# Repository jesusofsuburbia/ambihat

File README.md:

# Ambihat

### Raspberry Pi Hat to connect neopixels as ambilight and an IR receiver to remote control Kodi

... description follows ...

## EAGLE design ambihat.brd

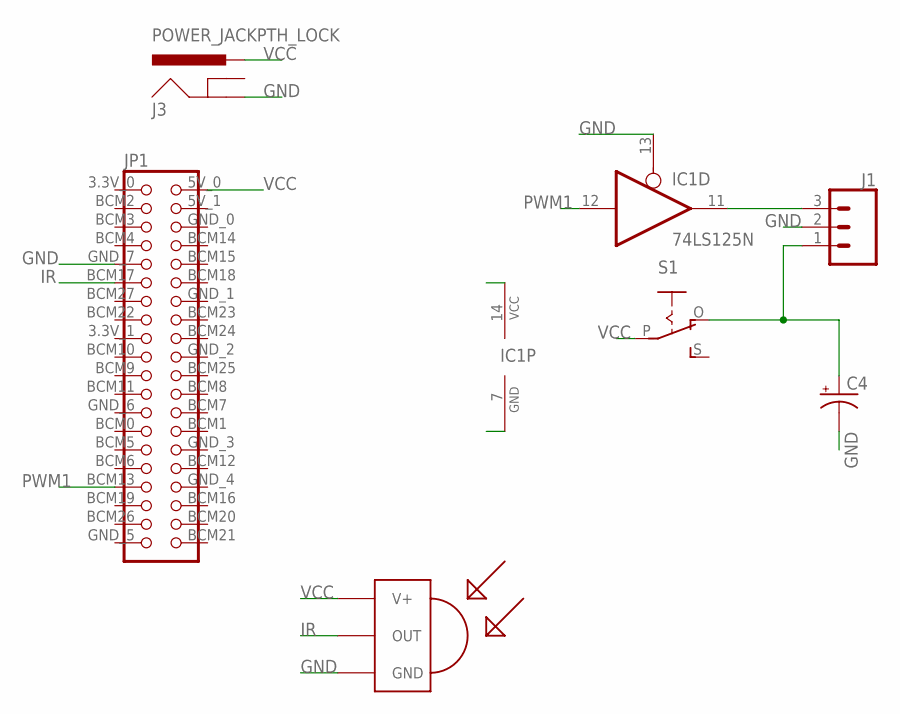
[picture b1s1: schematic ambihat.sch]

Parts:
C4: CPOL-USE5-10.5; E5-10,5
IC1: 74LS125N; DIL14
J1: CONN_03JST-PTH-VERT; JST-3-PTH-VERT
J3: POWER_JACKPTH_LOCK; POWER_JACK_PTH_LOCK
JP1: RASPBERRY-HEADER
S1: EG1218S; EG1218
U$1: TSOP4838; TSOP18XX

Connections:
GND: C4.-, IC1.7 (GND), IC1.13 (OE), J1.2, J3.GND, JP1.GND_7 (9_GND), U$1.GND
IR: JP1.BCM17 (11_BCM17), U$1.OUT
unnamed: IC1.11 (O), J1.3
unnamed: C4.+, J1.1, S1.O
PWM1: IC1.12 (I), JP1.BCM13 (33_BCM13_PWM1)
VCC: IC1.14 (VCC), J3.PWR, JP1.5V_0 (5V_1), S1.P, U$1.VCC (V+)

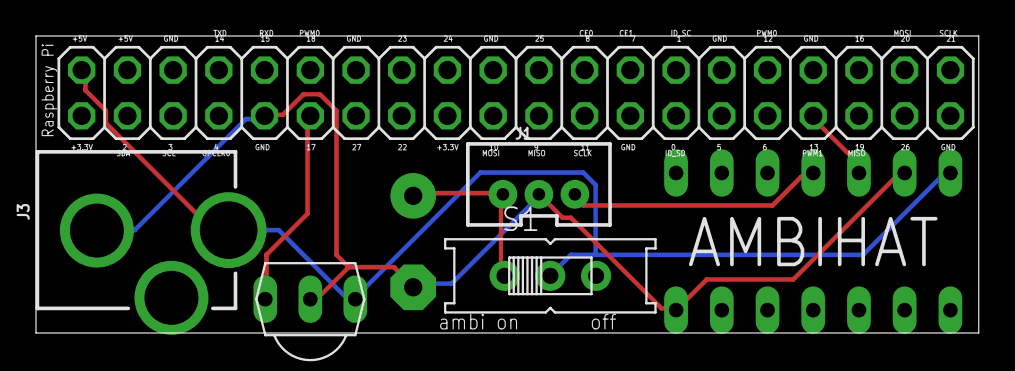
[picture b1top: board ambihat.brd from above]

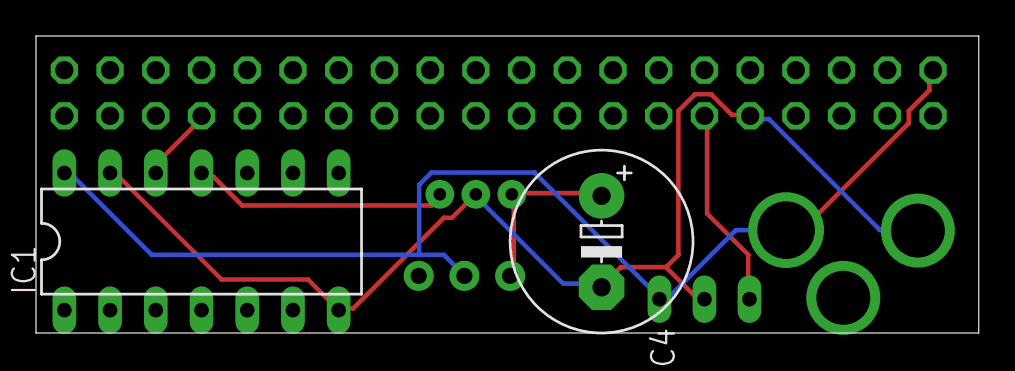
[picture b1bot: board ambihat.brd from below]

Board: 2 copper layers, 52.4 x 16.5 mm, 7 parts (2 on the bottom side), 6 nets.

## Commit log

2017-02-25 initial commit with hopefully all files

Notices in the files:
parts and their libraries:
SparkFun-Connectors: Licensing: Creative Commons ShareAlike 4.0 International - https://creativecommons.org/licenses/by-sa/4.0
